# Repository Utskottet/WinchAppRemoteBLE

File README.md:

# ParaWinch

Paragliding winch control system. The winch controller communicates with a handheld remote over 868 MHz LoRa. The remote also connects via BLE to a phone app for monitoring and configuration.

**Phone app:** https://utskottet.github.io/parawinch/

## Repository structure

| Folder | Description | Hardware |
|--------|-------------|----------|
| `winch/` | Winch controller firmware | M5Stack Core (ESP32) + Waveshare LoRa 868 MHz |
| `remote/` | Handheld remote firmware | Seeed XIAO nRF52840 + Wio SX1262 |
| `sim/` | LoRa simulator — mimics winch transmissions for development without the winch | Seeed XIAO nRF52840 + Wio SX1262 |
| `archive/itsy-bitsy/` | Old test firmware, not in use | Adafruit ItsyBitsy |
| `docs/` | System specifications and notes | — |

## Communication

```
Phone  <── BLE ──>  Remote (Xiao nRF52840)  <── 868 MHz LoRa ──>  Winch (M5Stack ESP32)
```

## Docs

- [Specifications](docs/specifications.md)
- [Upgrade plan](docs/upgrade_plan.md)
- [Force calibration plan](docs/winch_force_calibration_plan.md)
- [Antenna tests](docs/antenna_tests.md)
- [Lisp scripts](docs/lisp.txt)

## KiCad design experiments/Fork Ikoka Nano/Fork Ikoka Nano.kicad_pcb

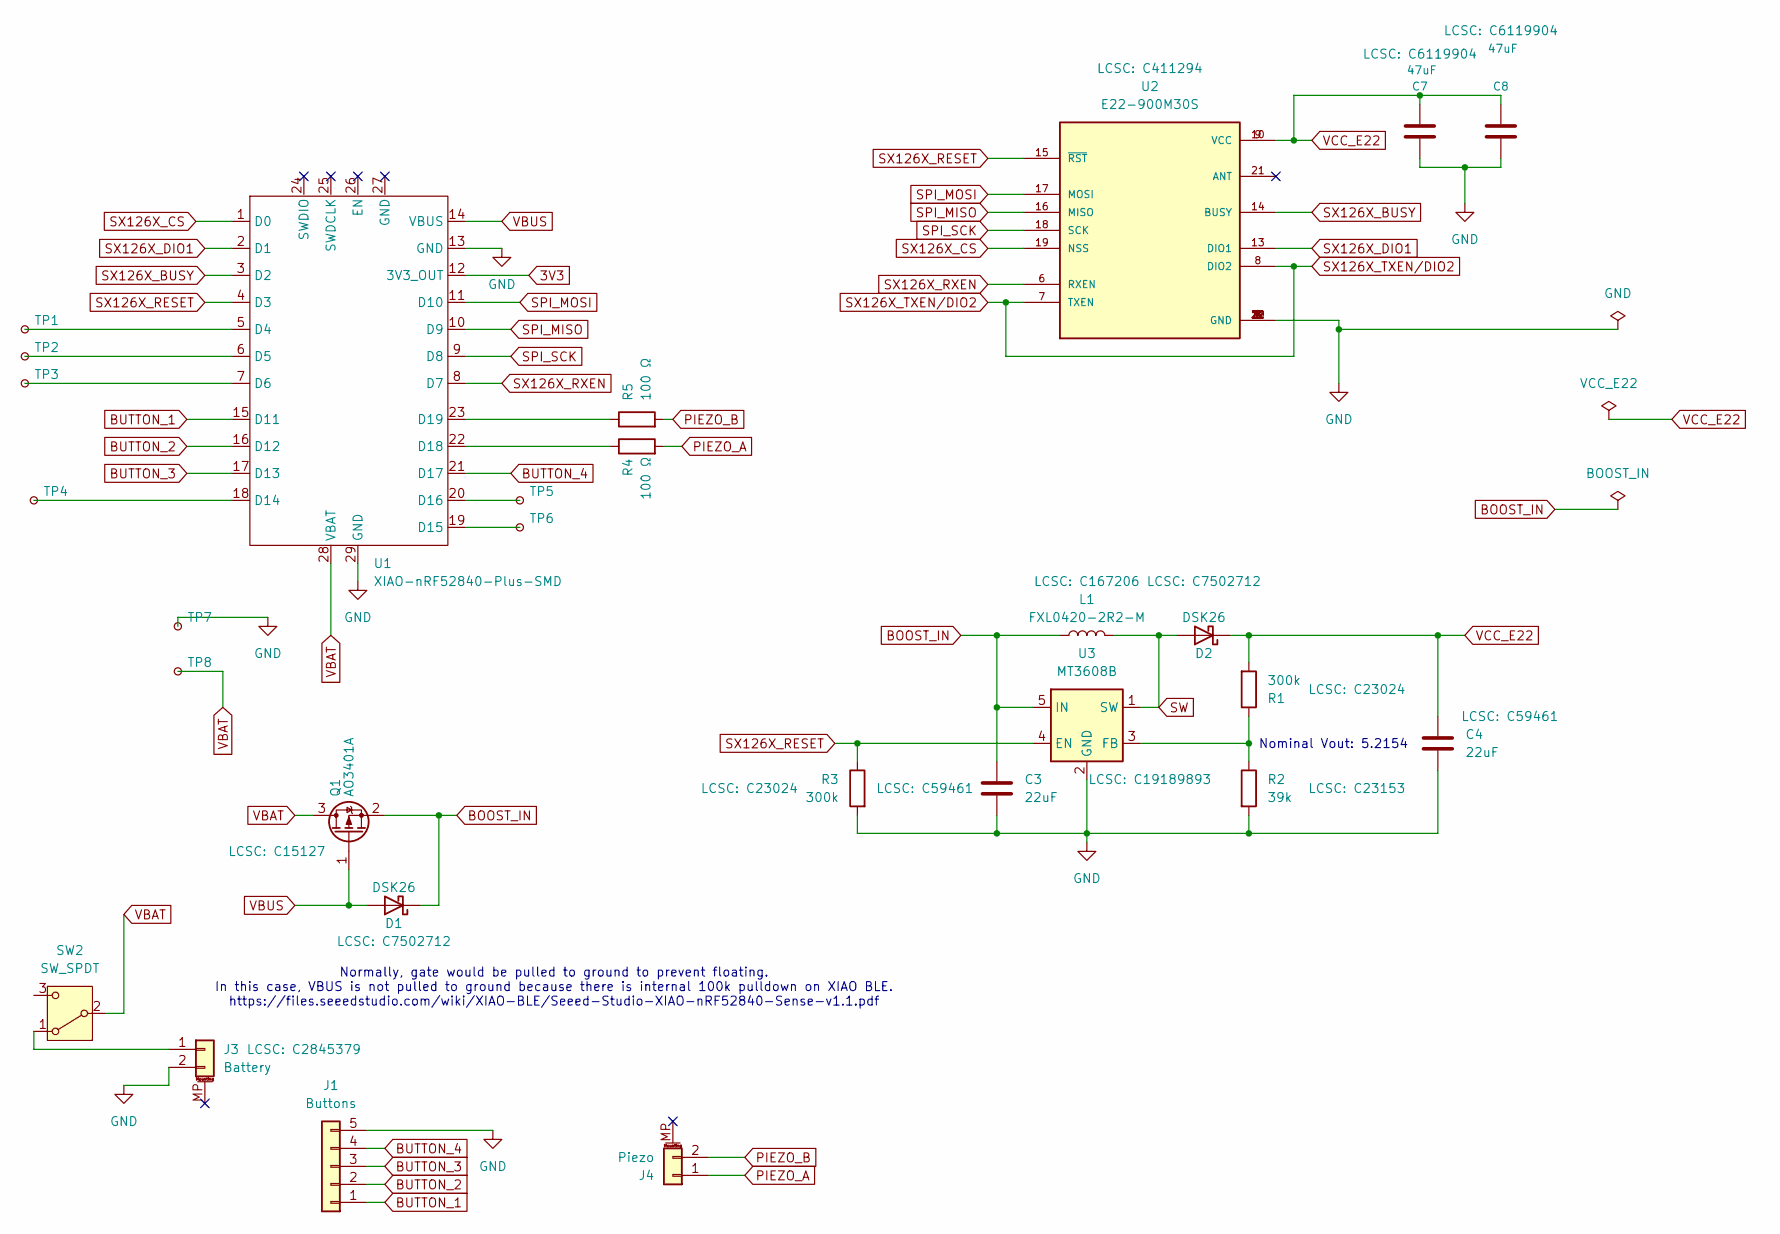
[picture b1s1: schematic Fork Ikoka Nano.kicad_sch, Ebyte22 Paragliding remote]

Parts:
C3, C4: 22uF; C_0603_1608Metric_Pad1.08x0.95mm_HandSolder; MPN CL10A226MQ8NRNC; LCSC C59461
C7, C8: 47uF; C_0805_2012Metric_Pad1.18x1.45mm_HandSolder; MPN CGA0805X5R476M100MT; LCSC C6119904
D1, D2: DSK26; D_SOD-123F; LCSC C7502712
J1: Buttons; Molex_PicoBlade_53047-0510_1x05_P1.25mm_Vertical
J3: Battery; Molex_PicoBlade_53261-0271_1x02-1MP_P1.25mm_Horizontal; LCSC C2845379
J4: Piezo; SolderWire-0.15sqmm_1x02_P4mm_D0.5mm_OD1.5mm
L1: FXL0420-2R2-M; L_Changjiang_FXL0420; MPN FXL0420-2R2-M; LCSC C167206
Q1: AO3401A; SOT-23; LCSC C15127
R1, R3: 300k; R_0603_1608Metric_Pad0.98x0.95mm_HandSolder; MPN 0603WAF3003T5E; LCSC C23024
R2: 39k; R_0603_1608Metric_Pad0.98x0.95mm_HandSolder; MPN 0603WAF3902T5E; LCSC C23153
R4, R5: 100 Ω; R_0603_1608Metric_Pad0.98x0.95mm_HandSolder; MPN 0603WAF1000T5E; LCSC C22775
SW2: SW_SPDT; SW_SPDT_PCM12
TP1, TP2, TP3, TP4, TP5, TP6: TestPoint_Small; TestPoint_Pad_D1.0mm
TP7, TP8: TestPoint_Small; TestPoint_THTPad_2.0x2.0mm_Drill1.0mm
U1: XIAO-nRF52840-Plus-SMD
U2: E22-900M30S; XCVR_E22-900M30S; PARTREV 1.2; LCSC C411294
U3: MT3608B; SOT-23-6; LCSC C19189893

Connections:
3V3: U1.12 (3V3_OUT)
BOOST_IN: C3.1, D1.1 (K), L1.1, Q1.2 (S), U3.5 (IN)
BUTTON_1: J1.1, U1.15 (D11)
BUTTON_2: J1.2, U1.16 (D12)
BUTTON_3: J1.3, U1.17 (D13)
BUTTON_4: J1.4, U1.21 (D17)
GND: C3.2, C4.2, C7.1, C8.1, J1.5, J3.2, R2.2, R3.2, TP7.1 (1_1), U1.13 (GND), U1.29 (GND), U2.1 (GND), U2.2 (GND), U2.3 (GND), U2.4 (GND), U2.5 (GND), U2.11 (GND), U2.12 (GND), U2.20 (GND), U2.22 (GND), U3.2 (GND); also elsewhere on the board
unnamed: J3.1, SW2.1 (A)
unnamed: TP1.1 (1_1), U1.5 (D4)
unnamed: TP2.1 (1_1), U1.6 (D5)
unnamed: TP3.1 (1_1), U1.7 (D6)
unnamed: TP4.1 (1_1), U1.18 (D14)
unnamed: TP6.1 (1_1), U1.19 (D15)
unnamed: TP5.1 (1_1), U1.20 (D16)
unnamed: R4.1, U1.22 (D18)
unnamed: R5.1, U1.23 (D19)
unnamed: R1.1, R2.1, U3.3 (FB)
PIEZO_A: J4.1, R4.2
PIEZO_B: J4.2, R5.2
SPI_MISO: U1.10 (D9), U2.16 (MISO)
SPI_MOSI: U1.11 (D10), U2.17 (MOSI)
SPI_SCK: U1.9 (D8), U2.18 (SCK)
SW: D2.2 (A), L1.2, U3.1 (SW)
SX126X_BUSY: U1.3 (D2), U2.14 (BUSY)
SX126X_CS: U1.1 (D0), U2.19 (NSS)
SX126X_DIO1: U1.2 (D1), U2.13 (DIO1)
SX126X_RESET: R3.1, U1.4 (D3), U2.15 (~RST), U3.4 (EN)
SX126X_RXEN: U1.8 (D7), U2.6 (RXEN)
SX126X_TXEN/DIO2: U2.7 (TXEN), U2.8 (DIO2)
VBAT: Q1.3 (D), SW2.2 (B), TP8.1 (1_1), U1.28 (VBAT)
VBUS: D1.2 (A), Q1.1 (G), U1.14 (VBUS)
VCC_E22: C4.1, C7.2, C8.2, D2.1 (K), R1.2, U2.9 (VCC), U2.10 (VCC); also elsewhere on the board

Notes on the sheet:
Nominal Vout: 5.2154
Normally, gate would be pulled to ground to prevent floating. In this case, VBUS is not pulled to ground because there is internal 100k pulldown on XIAO BLE. https://files.seeedstudio.com/wiki/XIAO-BLE/Seeed-Studio-XIAO-nRF52840-Sense-v1.1.pdf

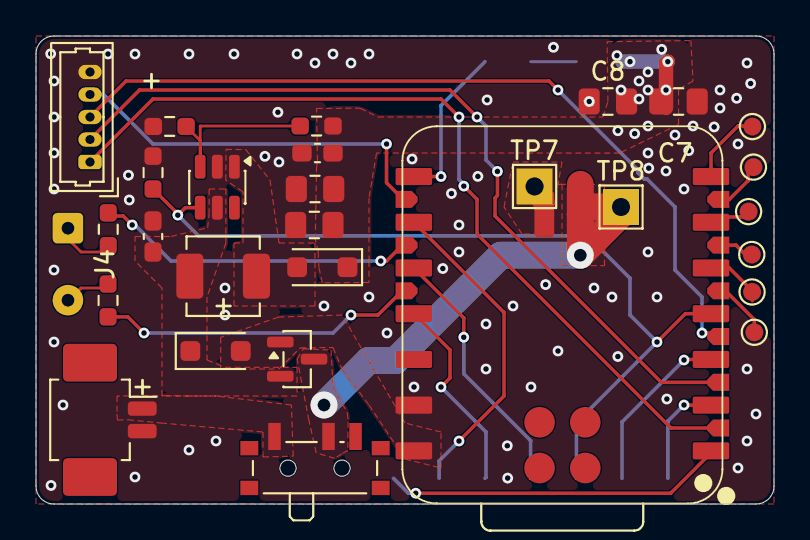
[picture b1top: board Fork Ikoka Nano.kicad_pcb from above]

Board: 2 copper layers, 41.0 x 26.0 mm, 30 parts (1 on the bottom side), 31 nets.

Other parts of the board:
C1, C2: 47uF; C_0805_2012Metric_Pad1.18x1.45mm_HandSolder

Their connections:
GND: C1.1, C2.1; also elsewhere on the board
VCC_E22: C1.2, C2.2; also elsewhere on the board

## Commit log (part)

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2026-01-10 Update index.html
    horizontal
2026-01-10 Update index.html
    new ui
2026-01-10 Update index.html
    bump
2026-01-10 Add files via upload
    Added Itsy bitsy firmware
2026-01-10 Add files via upload
    wrong folder
2026-04-28 Restructure into monorepo
    - remote/ Xiao remote firmware
    - winch/ ESP winch controller (from 868-ParaWinch)
    - sim/ XiaoWinchSim dev helper
    - archive/ ItsyBitsy (unused)
    - docs/ antenna_tests.md spec
    - root phone app (GitHub Pages)
2026-04-28 Update README with correct structure and hardware info
2026-04-28 Add Waveshare LoRa 868 module to winch hardware info
2026-04-28 Add project documents to docs/
2026-04-28 Update README with links to key documents
2026-04-28 Add battery.md to docs
